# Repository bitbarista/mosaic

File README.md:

# MOSaic — an FPGA replacement for the C64's 6510 CPU

<div align="center">

</div>

MOSaic is a drop-in replacement for the Commodore 64's 6510 CPU. It plugs into the 6510
socket and behaves like the original chip, cycle for cycle, undocumented opcodes and quirks
included. Inside is a Lattice iCE40UP5K FPGA, checked against a transistor-level simulation
of the real chip and against VICE's test suite on a real C64.

> **Free for non-commercial use.** MOSaic is a hobby project, given to the community.
> If it's useful to you, please consider [supporting it on Ko-fi](https://ko-fi.com/bitbarista).
> It funds the prototypes and test hardware.
> Want to sell boards? See [Commercial use](#commercial-use).
>
> **Ordering boards?** Signing up to JLCPCB through [this referral link](https://jlcpcb.com/?from=PBTJYEXOJNFQR) costs you nothing
> extra and earns the project a small credit towards new prototypes.

## Status (Rev A, October 2026)

On a real C64 with the current build (`$2ECB`):

- **VICE testprogs** (interrupts, CIA, VIC-II, CPU): all 169 pass, including the undocumented
  opcodes and the SHA/SHX/SHY/TAS behaviour during badlines (one unrepeated mismatch is noted
  under Known limits). The 16 `ciavarious` CIA tests report on screen only, so they were checked by eye
  (`test-results/hardware/ciavarious_2ecb_20261019.log`). The full comparison is in
  `test-results/hardware/hw_2ecb_vs_e4e7_3e5d_20261014.txt`.
- **Demos:** a four-disk demo (NLP) runs all the way through, using a stock KERNAL and JiffyDOS.
- **[DRAMscope](https://github.com/bitbarista/dramscope)** (a C64 RAM tester that drives the
  memory bus through the CPU): 48 passes in an hour with no bad bytes.

In simulation:

- Klaus Dormann's functional test and the Lorenz test suite pass.
- Every bus cycle is compared with **perfect6502** (a transistor-level simulation of the
  real chip). This covers sweeps of interrupt timing against RDY stalls, the undocumented
  SH* opcodes, and double NMIs.

**Known limits.** These are listed openly; the details are in
[docs/KNOWN-ISSUES.md](docs/KNOWN-ISSUES.md).

- `interrupts/irqdma/test6b` gave one mismatch in 96 runs and could not be reproduced. The
  VICE testbench developers haven't seen this test misbehave before, though other tests in
  the testbench have needed fixing over the years. Run logs are in `test-results/hardware/`.
- The electrical checks against the 6510's AC and DC datasheet tables flag a few deviations,
  none seen to cause a fault. See `docs/KNOWN-ISSUES.md`.
- Tested in one C64 so far. The C64C (8500) has not been checked. It does **not** fit a 1541
  or a C128, whose CPUs have different pinouts.

## How it works

- **The CPU core** is T65, a VHDL 65xx core (FPGAARCADE 2015 release, BSD-3). Its upstream
  copyright and licence are kept, and the local fixes are listed in `NOTICE` and `patches/`.
- **The 6510 wrapper** — the I/O port, bus timing and RDY/AEC handling — is written from
  the 6510 datasheet: `rtl/cpu6510.v` and `rtl/top.v`.
- **Firmware updates** run on the C64 itself: a program writes a new image into a spare
  slot and checks it before switching. Power-on always boots slot A. See `updater/`.

## Building one

1. **Order the boards** from JLCPCB ([referral link](https://jlcpcb.com/?from=PBTJYEXOJNFQR)), fully assembled: `hardware/jlcpcb-reva/` holds the
   gerbers, BOM and placement file. `hardware/jlcpcb-reva/ORDERING.md` lists the options to choose.
2. **Fit the parts JLCPCB doesn't**: the 40 turned plug pins, soldered straight with the
   3D-printed jig, and the J4 update header. See **[docs/ASSEMBLY.md](docs/ASSEMBLY.md)**.
3. **Program it once**, then fit it in the C64. See
   **[docs/PROGRAMMING.md](docs/PROGRAMMING.md)**.

### Programming and updates

**[docs/PROGRAMMING.md](docs/PROGRAMMING.md)** is the step-by-step guide. It covers the
programmer and probe wiring, the first flash, fitting the board in the C64 and updating it
from the C64.

A new board is programmed **once**, on the bench, from a **Linux** PC, with an FT232H and a 1.27 mm pogo probe on
J3. Start `syn/pogo.sh --usb-last` first. It talks you through it hands-free: **seat the probe,
then plug the programmer's USB in last**.
After that, every update runs on the C64 itself, from `updater/out/MOSAIC.D64`.

### Building from source

- **Gateware:** run `syn/synth.sh`. This needs Yosys and nextpnr (OSS CAD Suite). From this
  source it reproduces `syn/build/mosaic.bin`, build ID `$2ECB`, md5
  `6a16527c77c44bc291d11e6a1fa41198`.
- **Test records:** the hardware run logs and the full simulation gate log are in
  `test-results/`, with a README saying what each one shows.

## Documents

| File | What |
|---|---|
| `docs/ASSEMBLY.md` | Parts to fit by hand (plug pins, J4), the soldering jig, order of work |
| `docs/PROGRAMMING.md` | First programming, fitting in the C64, updates |
| `docs/KNOWN-ISSUES.md` | Operating rules, datasheet deviations, what is not yet tested |
| `hardware/jlcpcb-reva/ORDERING.md` | JLCPCB order settings and parts |
| `test-results/README.md` | The raw test records: hardware runs and the simulation gate |
| `NOTICE` | Third-party code and its licences |

Comments in the source cite entries such as E-39, D-16 or S-19, and check scripts under `sim/`
and `gen/`. These are in the project's development tree, which is not published. The fixes they describe
are summarised in `NOTICE` and `patches/`, and the test results are in `test-results/`.

## Support the project

MOSaic took months of design work and several rounds of prototype boards. If you build one,
or it saved you hunting for a working 6510, a coffee on Ko-fi is very welcome:

New to JLCPCB? Signing up through [this referral link](https://jlcpcb.com/?from=PBTJYEXOJNFQR) also helps: it earns the project
a small credit towards new prototypes, at no cost to you.

## Commercial use

The licences below allow personal, non-commercial use: build one for yourself or a friend,
modify it, share your changes. **Selling boards, kits or pre-programmed parts needs a
commercial licence** — get in touch through [Ko-fi](https://ko-fi.com/bitbarista) or open a
GitHub issue titled "Commercial licence", and we can agree terms.

## Disclaimer

MOSaic is a hobby project, provided as is, without warranty of any kind. Building,
programming and fitting it is at your own risk. The author accepts no responsibility for
damage to your C64, its socket, the original 6510, other hardware or data, or for any
other loss. Check your work before powering up, and read [docs/ASSEMBLY.md](docs/ASSEMBLY.md) before fitting
the plug pins. The full terms are in the licences below.

## Licence

© 2026 Carl Leach. Free for non-commercial use, under two licences:

- **Hardware design and documentation:** [CC BY-NC-SA 4.0](LICENSES/CC-BY-NC-SA-4.0.txt)
- **Gateware, firmware and tools:** [PolyForm Noncommercial 1.0.0](LICENSES/PolyForm-Noncommercial-1.0.0.md)

Third-party code keeps its own licence: the T65 core and the patches to it are BSD-3
(`rtl/t65/`, `patches/`). [LICENSE.md](LICENSE.md) says which licence covers which folder, and
`NOTICE` has the third-party notices.

*Not affiliated with, or endorsed by, any holder of the Commodore trademarks.*

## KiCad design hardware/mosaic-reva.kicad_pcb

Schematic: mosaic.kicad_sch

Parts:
C1, C2, C3, C4, C5, C6, C7, C8, C9, C10, C11, C12, C13, C14: 100n; C_0402_1005Metric
C15, C16, C17: 4u7; C_0603_1608Metric
C18, C19, C20, C21: 1u; C_0402_1005Metric
D1: SMF6.0A; D_SOD-123F
D2, D3: B5819W; D_SOD-123
J1: plug pins, 6510 pins 1-20 -- Switch Electronics 5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; PlugHeader_1x20_P2.54mm_Machined
J2: plug pins, 6510 pins 21-40 -- Switch Electronics 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; PlugHeader_1x20_P2.54mm_Machined
J3: programming PADS for a pogo jig -- the iCEBreaker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; ProgPads_1x07_P1.27mm
J4: PROG_EN jumper -- bridge to enable flash writes (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; PinHeader_1x02_P2.54mm_Vertical
R1, R2, R3, R4: 10k; R_0402_1005Metric
RN1, RN2, RN3, RN4, RN5, RN6, RN7, RN8: 33R x4 array; R_Array_Convex_4x0402
TP1: CDONE; TestPoint_Pad_D1.0mm
U1: ICE40UP5K-SG48I; QFN-48-1EP_7x7mm_P0.5mm_EP5.6x5.6mm
U2, U3: SN74CB3T3245PWR; TSSOP-20_4.4x6.5mm_P0.65mm
U4, U5: SN74LVC541ADGVR; TSSOP-20_4.4x5mm_P0.4mm
U6, U11: SN74LVC1G125DCKR; SOT-353_SC-70-5
U7: SN74LVC14APWR; TSSOP-14_4.4x5mm_P0.65mm
U8: W25Q16JVUXIQ; Winbond_USON-8-1EP_3x2mm_P0.5mm_EP0.2x1.6mm
U9: NCP115ASN330T2G; SOT-23-5
U10: ME6211C12M5G-N; SOT-23-5

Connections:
+1V2: C1.1, C2.1, C17.1, C19.1, U1.5 (VCC), U1.29 (VCCPLL), U1.30 (VCC), U9.3 (EN), U10.5 (OUT)
+3V3: C3.1, C4.1, C5.1, C6.1, C7.1, C8.1, C9.1, C10.1, C11.1, C12.1, C13.1, C14.1, C16.1, C21.1, R1.1, R2.1, R3.1, R4.1, U1.1 (VCCIO_2), U1.22 (SPI_VCCIO1), U1.24 (VPP_2V5), U1.33 (VCCIO_0), U2.20 (VCC), U3.20 (VCC), U4.20 (VCC), U5.20 (VCC), U6.5 (VCC), U7.14 (VCC), U8.3 (~WP/IO2), U8.7 (~HOLD/IO3), U8.8 (VCC), U9.5 (OUT), U11.5 (VCC)
+5V: C15.1, C18.1, C20.1, D2.1 (K), D3.1 (K), U9.1 (IN), U10.1 (IN), U10.3 (EN)
+5V_SKT: D1.1 (A1), D2.2 (A), J1.6
/CDONE: R3.2, TP1.1, U1.7 (CDONE)
/CRESET_N: J3.7, R1.2, U1.8 (~CRESET)
A0: U1.13 (IOB_24a), U4.2 (A0)
A1: U1.18 (IOB_31b), U4.3 (A1)
A2: U1.19 (IOB_29b), U4.4 (A2)
A3: U1.20 (IOB_25b_G3), U4.5 (A3)
A4: U1.21 (IOB_23b), U4.6 (A4)
A5: U1.23 (IOT_37a), U4.7 (A5)
A6: U1.11 (IOB_20a), U4.8 (A6)
A7: U1.12 (IOB_22a), U4.9 (A7)
A8: U1.2 (IOB_6a), U5.2 (A0)
A9: U1.3 (IOB_9b), U5.3 (A1)
A10: U1.4 (IOB_8a), U5.4 (A2)
A11: U1.6 (IOB_13b), U5.5 (A3)
A12: U1.9 (IOB_16a), U5.6 (A4)
A13: U1.10 (IOB_18a), U5.7 (A5)
A14: U1.28 (IOT_41a), U5.9 (A7)
A15: U1.31 (IOT_42b), U5.8 (A6)
AEC_N: U1.35 (IOT_46b_G0), U4.1 (G1), U4.19 (G2), U5.1 (G1), U5.19 (G2), U6.1, U7.10
C64_A0: J1.7, RN1.1 (R1.1)
C64_A0_R: RN1.8 (R1.2), U4.18 (Y0)
C64_A1: J1.8, RN1.2 (R2.1)
C64_A1_R: RN1.7 (R2.2), U4.17 (Y1)
C64_A2: J1.9, RN1.3 (R3.1)
C64_A2_R: RN1.6 (R3.2), U4.16 (Y2)
C64_A3: J1.10, RN1.4 (R4.1)
C64_A3_R: RN1.5 (R4.2), U4.15 (Y3)
C64_A4: J1.11, RN2.1 (R1.1)
C64_A4_R: RN2.8 (R1.2), U4.14 (Y4)
C64_A5: J1.12, RN2.2 (R2.1)
C64_A5_R: RN2.7 (R2.2), U4.13 (Y5)
C64_A6: J1.13, RN2.3 (R3.1)
C64_A6_R: RN2.6 (R3.2), U4.12 (Y6)
C64_A7: J1.14, RN2.4 (R4.1)
C64_A7_R: RN2.5 (R4.2), U4.11 (Y7)
C64_A8: J1.15, RN3.1 (R1.1)
C64_A8_R: RN3.8 (R1.2), U5.18 (Y0)
C64_A9: J1.16, RN3.2 (R2.1)
C64_A9_R: RN3.7 (R2.2), U5.17 (Y1)
C64_A10: J1.17, RN3.3 (R3.1)
C64_A10_R: RN3.6 (R3.2), U5.16 (Y2)
C64_A11: J1.18, RN3.4 (R4.1)
C64_A11_R: RN3.5 (R4.2), U5.15 (Y3)
C64_A12: J1.19, RN4.1 (R1.1)
C64_A12_R: RN4.8 (R1.2), U5.14 (Y4)
C64_A13: J1.20, RN4.2 (R2.1)
C64_A13_R: RN4.7 (R2.2), U5.13 (Y5)
C64_A14: J2.2, RN8.2 (R2.1)
C64_A14_R: RN8.7 (R2.2), U5.11 (Y7)
C64_A15: J2.3, RN8.1 (R1.1)
C64_A15_R: RN8.8 (R1.2), U5.12 (Y6)
C64_AEC: J1.5, U7.11
C64_D0: J2.17, RN5.3 (R3.1)
C64_D0_R: RN5.6 (R3.2), U2.18 (B1)
C64_D1: J2.16, RN5.4 (R4.1)
C64_D1_R: RN5.5 (R4.2), U2.17 (B2)
C64_D2: J2.15, RN6.1 (R1.1)
C64_D2_R: RN6.8 (R1.2), U2.16 (B3)
C64_D3: J2.14, RN6.2 (R2.1)
C64_D3_R: RN6.7 (R2.2), U2.15 (B4)
C64_D4: J2.13, RN6.3 (R3.1)
C64_D4_R: RN6.6 (R3.2), U2.14 (B5)
C64_D5: J2.12, RN6.4 (R4.1)
C64_D5_R: RN6.5 (R4.2), U2.13 (B6)
C64_D6: J2.11, RN7.1 (R1.1)
C64_D6_R: RN7.8 (R1.2), U2.12 (B7)
C64_D7: J2.10, RN7.2 (R2.1)
C64_D7_R: RN7.7 (R2.2), U2.11 (B8)
C64_IRQ_N: J1.3, U7.5
C64_NMI_N: J1.4, U7.9
C64_P0: J2.9, U3.18 (B1)
C64_P1: J2.8, U3.17 (B2)
C64_P2: J2.7, U3.16 (B3)
C64_P3: J2.6, U3.15 (B4)
C64_P4: J2.5, U3.14 (B5)
C64_P5: J2.4, U3.13 (B6)
C64_PHI0: J1.1, U7.1
C64_PHI2: J2.19, RN5.1 (R1.1)
C64_PHI2_R: RN5.8 (R1.2), U11.4
C64_RDY: J1.2, U7.3
C64_RES_N: J2.20, U7.13
C64_RW: J2.18, RN5.2 (R2.1)
C64_RW_R: RN5.7 (R2.2), U6.4
D0: U1.37 (IOT_45a_G1), U2.2 (A1)
D1: U1.38 (IOT_50b), U2.3 (A2)
D2: U1.42 (IOT_51a), U2.4 (A3)
D3: U1.43 (IOT_49a), U2.5 (A4)
D4: U1.45 (IOB_5b), U2.6 (A5)
D5: U1.46 (IOB_0a), U2.7 (A6)
D6: U1.47 (IOB_2a), U2.8 (A7)
D7: U1.48 (IOB_4a), U2.9 (A8)
GND: C1.2, C2.2, C3.2, C4.2, C5.2, C6.2, C7.2, C8.2, C9.2, C10.2, C11.2, C12.2, C13.2, C14.2, C15.2, C16.2, C17.2, C18.2, C19.2, C20.2, C21.2, D1.2 (A2), J2.1, J3.2, J4.2, U1.49 (GND), U2.10 (GND), U2.19 (~OE), U3.10 (GND), U3.19 (~OE), U4.10 (GND), U5.10 (GND), U6.3 (GND), U7.7 (GND), U8.4 (GND), U8.9 (EP), U9.2 (GND), U10.2 (GND), U11.1, U11.3 (GND)
IRQ_N: U1.39 (RGB0), U7.6
NC_U3_6: U3.8 (A7), U3.12 (B7)
NC_U3_7: U3.9 (A8), U3.11 (B8)
NMI_N: U1.40 (RGB1), U7.8
P0: U1.25 (IOT_36b), U3.2 (A1)
P1: U1.26 (IOT_39a), U3.3 (A2)
P2: J3.5, U1.14 (IOB_32a_SPI_SO), U3.4 (A3), U8.5 (DI/IO0)
P3: J3.6, U1.17 (IOB_33b_SPI_SI), U3.5 (A4), U8.2 (DO/IO1)
P4: J4.1, U1.27 (IOT_38b), U3.6 (A5)
P5: J3.4, R4.2, U1.15 (IOB_34a_SPI_SCK), U3.7 (A6), U8.6 (CLK)
PHI0_N: U1.44 (IOB_3b_G6), U7.2
PHI2: U1.34 (IOT_44b), U11.2
RDY_N: U1.36 (IOT_48b), U7.4
RES_N: U1.41 (RGB2), U7.12
RW: U1.32 (IOT_43a), U6.2
SPI_CS_N: J3.3, R2.2, U1.16 (IOB_35b_SPI_SS), U8.1 (~CS)
VPROG: D3.2 (A), J3.1

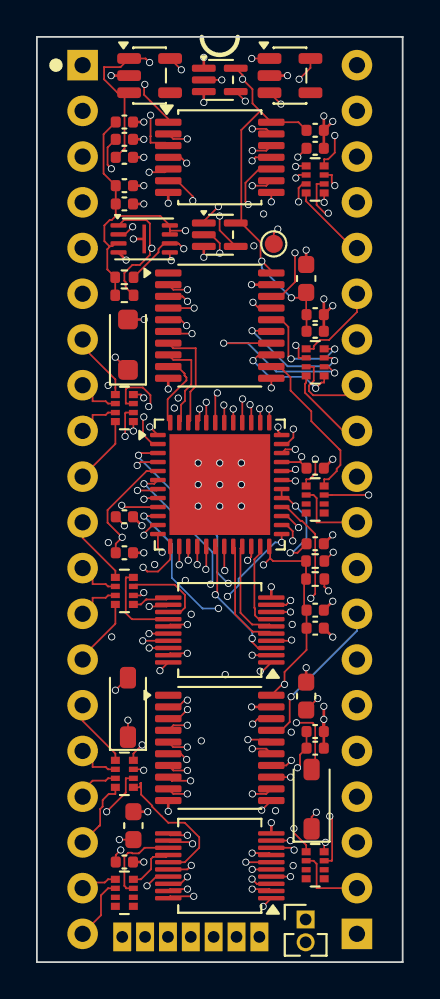
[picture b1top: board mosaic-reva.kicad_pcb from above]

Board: 4 copper layers, 20.3 x 51.4 mm, 52 parts (0 on the bottom side), 113 nets.

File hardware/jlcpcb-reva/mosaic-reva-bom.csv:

Comment,Designator,Footprint,LCSC Part #
100n,"C1,C10,C11,C12,C13,C14,C2,C3,C4,C5,C6,C7,C8,C9",C_0402_1005Metric,C1525
4u7,"C15,C16,C17",C_0603_1608Metric,C19666
1u,"C18,C19,C20,C21",C_0402_1005Metric,C52923
SMF6.0A,D1,D_SOD-123F,C178260
B5819W,"D2,D3",D_SOD-123,C8598
10k,"R1,R2,R3,R4",R_0402_1005Metric,C25744
33R x4 array,"RN1,RN2,RN3,RN4,RN5,RN6,RN7,RN8",R_Array_Convex_4x0402,C25501
ICE40UP5K-SG48I,U1,QFN-48-1EP_7x7mm_P0.5mm_EP5.6x5.6mm,C2678152
SN74CB3T3245PWR,"U2,U3",TSSOP-20_4.4x6.5mm_P0.65mm,C15298
SN74LVC541ADGVR,"U4,U5",TSSOP-20_4.4x5mm_P0.4mm,C2675530
SN74LVC1G125DCKR,"U11,U6",SOT-353_SC-70-5,C7833
SN74LVC14APWR,U7,TSSOP-14_4.4x5mm_P0.65mm,C7663
W25Q16JVUXIQ,U8,Winbond_USON-8-1EP_3x2mm_P0.5mm_EP0.2x1.6mm,C2843335
NCP115ASN330T2G,U9,SOT-23-5,C603505
ME6211C12M5G-N,U10,SOT-23-5,C236672

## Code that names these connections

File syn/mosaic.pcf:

# GENERATED by syn/gen_pcf.py from gen/design.py -- DO NOT EDIT.
# Every C64-facing pin is -pullup no; see the module docstring.

set_io -nowarn -pullup no A[8] 2
set_io -nowarn -pullup no A[9] 3
set_io -nowarn -pullup no A[10] 4
set_io -nowarn -pullup no A[11] 6
set_io -nowarn -pullup no A[12] 9
set_io -nowarn -pullup no A[13] 10
set_io -nowarn -pullup no A[6] 11
set_io -nowarn -pullup no A[7] 12
set_io -nowarn -pullup no A[0] 13
set_io -nowarn -pullup no P[2] 14
set_io -nowarn -pullup no P[5] 15
set_io -nowarn -pullup no SPI_CS_N 16
set_io -nowarn -pullup no P[3] 17
set_io -nowarn -pullup no A[1] 18
set_io -nowarn -pullup no A[2] 19
set_io -nowarn -pullup no A[3] 20
set_io -nowarn -pullup no A[4] 21
set_io -nowarn -pullup no A[5] 23
set_io -nowarn -pullup no P[0] 25
set_io -nowarn -pullup no P[1] 26
set_io -nowarn -pullup no P[4] 27
set_io -nowarn -pullup no A[14] 28
set_io -nowarn -pullup no A[15] 31
set_io -nowarn -pullup no RW 32
set_io -nowarn -pullup no PHI2 34
set_io -nowarn -pullup no AEC 35
set_io -nowarn -pullup no RDY 36
set_io -nowarn -pullup no D[0] 37
set_io -nowarn -pullup no D[1] 38
set_io -nowarn -pullup no IRQ_N 39
set_io -nowarn -pullup no NMI_N 40
set_io -nowarn -pullup no RES_N 41
set_io -nowarn -pullup no D[2] 42
set_io -nowarn -pullup no D[3] 43
set_io -nowarn -pullup no PHI0 44
set_io -nowarn -pullup no D[4] 45
set_io -nowarn -pullup no D[5] 46
set_io -nowarn -pullup no D[6] 47
set_io -nowarn -pullup no D[7] 48

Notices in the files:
README.md:
License: hardware
License: code
